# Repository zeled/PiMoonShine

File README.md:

# PiMoonShine
Все для автоматики Винокура на Orange PI PC+

Основано на Node-Red
18b20-mqtt - сервис опрашивающий 18b20 датчики и засылающий их в mqtt

---

## Установка Armbian на Orange PI PC+
https://www.armbian.com/orange-pi-pc-plus/

Устанавливаем Armbian Focal

Через armbian-config настраиваем сеть, доступ по ssh, timezone и т.д.

Там же в System-Hardware включаем i2c0, uart1, w1-gpio

## Установка Node-RED и необходимые пакеты
#### Заходим по SSH на OrangePi под рутом и запускаем:
```
bash <(curl -sL https://raw.githubusercontent.com/node-red/linux-installers/master/deb/update-nodejs-and-nodered)

apt-get update&&apt-get upgrade&&apt-get install mosquitto mosquitto-clients nginx

pip3 install paho-mqtt
pip3 install w1thermsensor
```
---
#### Копируем из папки 18b20-mqtt:

>18b20-mqtt в /usr/local/bin/

>18b20-mqtt.service в /etc/systemd/system/

#### Копируем из папки nginx:

>nodered в /etc/nginx/sites-enabled/

---
#### Запускаем:
`systemctl daemon-reload&&systemctl restart mosquitto 18b20-mqtt nodered nginx`

## Первоначальная Настройка

Заходим через браузер на http://<ip адресс orange-pi>/

Далее в "Управление палитрой"

#### Устанавилваем узлы:
>node-red-contrib-bme280
>
>node-red-contrib-configurable-interval
>
>node-red-contrib-mytimeout
>
>node-red-contrib-opi-gpio
>
>node-red-contrib-simpletime
>
>node-red-contrib-telegrambot
>
>node-red-contrib-ui-led
>
>node-red-contrib-ui-svg
>
>node-red-dashboard
>
>node-red-node-serialport

---

Импортируем проект из PiMoonShine.json

Настриваем telegram бота под свои данные.

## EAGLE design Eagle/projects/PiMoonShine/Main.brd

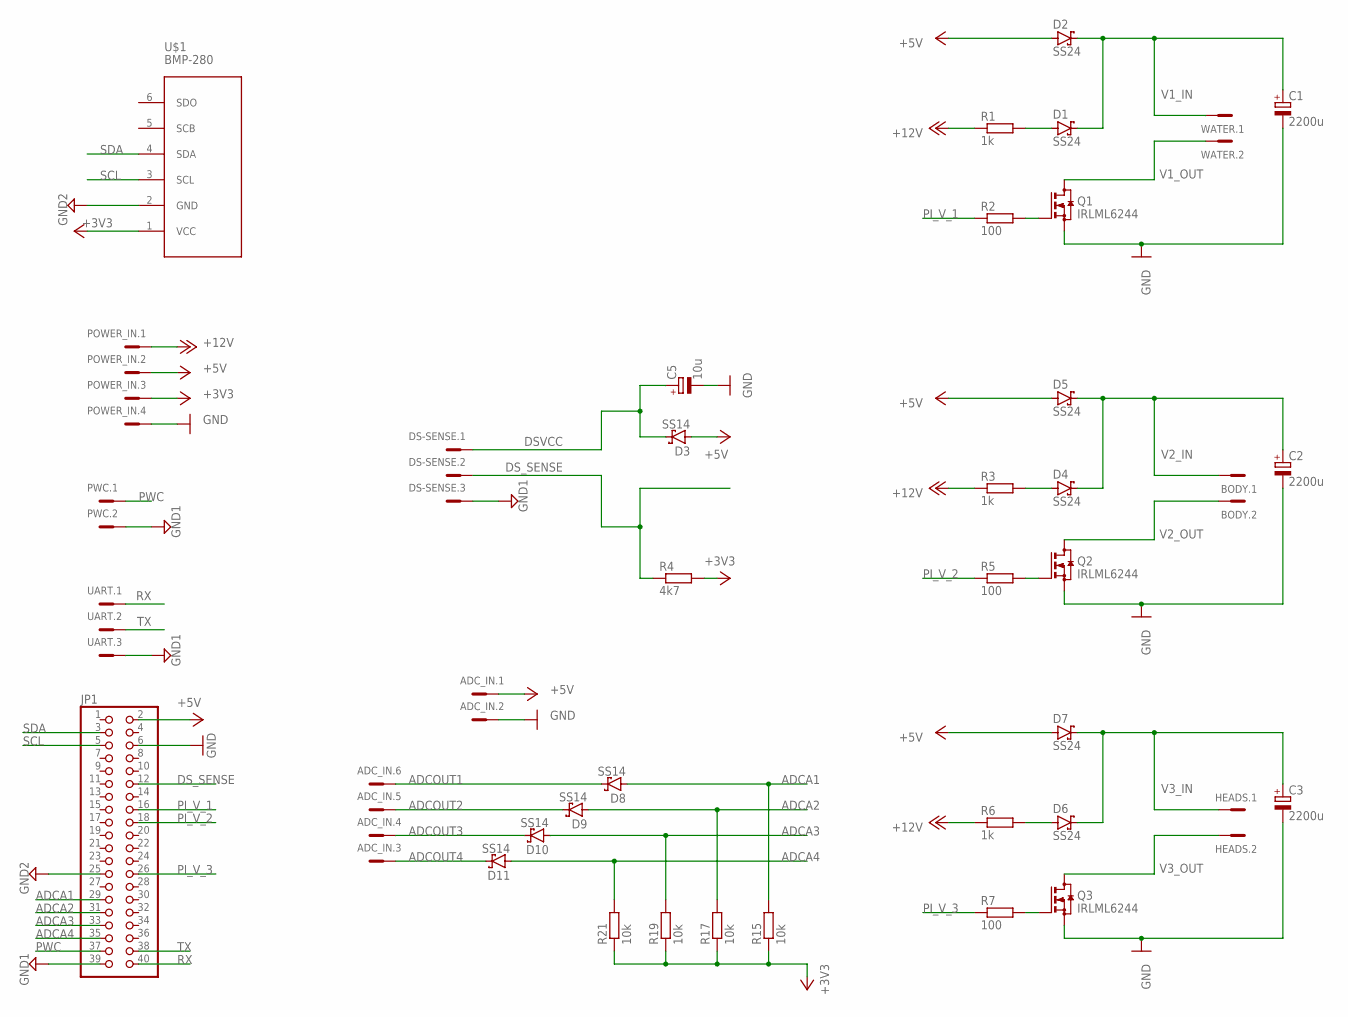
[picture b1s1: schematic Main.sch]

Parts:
ADC_IN: MCV6
BODY: MCV2
C1, C2, C3: 2200u; TT5D10
C5: 10u; SMC_B
D1, D2, D4, D5, D6, D7: SS24; SMB
D3, D8, D9, D10, D11: SS14; SMA
DS-SENSE: MCV3
HEADS: MCV2
JP1: PINHD-2X20; 2X20
POWER_IN: MCV4
PWC: MCV2
Q1, Q2, Q3: IRLML6244; SOT23
R1, R3, R6: 1k; R1206
R2, R5, R7: 100; R1206
R4: 4k7; R1206
R15, R17, R19, R21: 10k; R1206
U$1: BMP-280; BPM-280
UART: MCV3
WATER: MCV2

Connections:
+3V3: POWER_IN.3, R4.2, R15.1, R17.1, R19.1, R21.1, U$1.1 (VCC)
+5V: ADC_IN.1, D2.A, D3.A, D5.A, D7.A, JP1.2, POWER_IN.2
+12V: POWER_IN.1, R1.1, R3.1, R6.1
ADCA1: D8.A, JP1.29, R15.2
ADCA2: D9.A, JP1.31, R17.2
ADCA3: D10.A, JP1.33, R19.2
ADCA4: D11.A, JP1.35, R21.2
ADCOUT1: ADC_IN.6, D8.C
ADCOUT2: ADC_IN.5, D9.C
ADCOUT3: ADC_IN.4, D10.C
ADCOUT4: ADC_IN.3, D11.C
DSVCC: C5.+, D3.C, DS-SENSE.1
DS_SENSE: DS-SENSE.2, JP1.12, R4.1
GND: ADC_IN.2, C1.-, C2.-, C3.-, C5.-, JP1.6, POWER_IN.4, Q1.2 (S), Q2.2 (S), Q3.2 (S)
GND1: DS-SENSE.3, JP1.39, PWC.2, UART.3
GND2: JP1.25, U$1.2 (GND)
unnamed: D1.A, R1.2
unnamed: D4.A, R3.2
unnamed: Q1.1 (G), R2.2
unnamed: Q2.1 (G), R5.2
unnamed: D6.A, R6.2
unnamed: Q3.1 (G), R7.2
PI_V_1: JP1.16, R2.1
PI_V_2: JP1.18, R5.1
PI_V_3: JP1.26, R7.1
PWC: JP1.37, PWC.1
RX: JP1.40, UART.1
SCL: JP1.5, U$1.3 (SCL)
SDA: JP1.3, U$1.4 (SDA)
TX: JP1.38, UART.2
V1_IN: C1.+, D1.C, D2.C, WATER.1
V1_OUT: Q1.3 (D), WATER.2
V2_IN: BODY.1, C2.+, D4.C, D5.C
V2_OUT: BODY.2, Q2.3 (D)
V3_IN: C3.+, D6.C, D7.C, HEADS.1
V3_OUT: HEADS.2, Q3.3 (D)

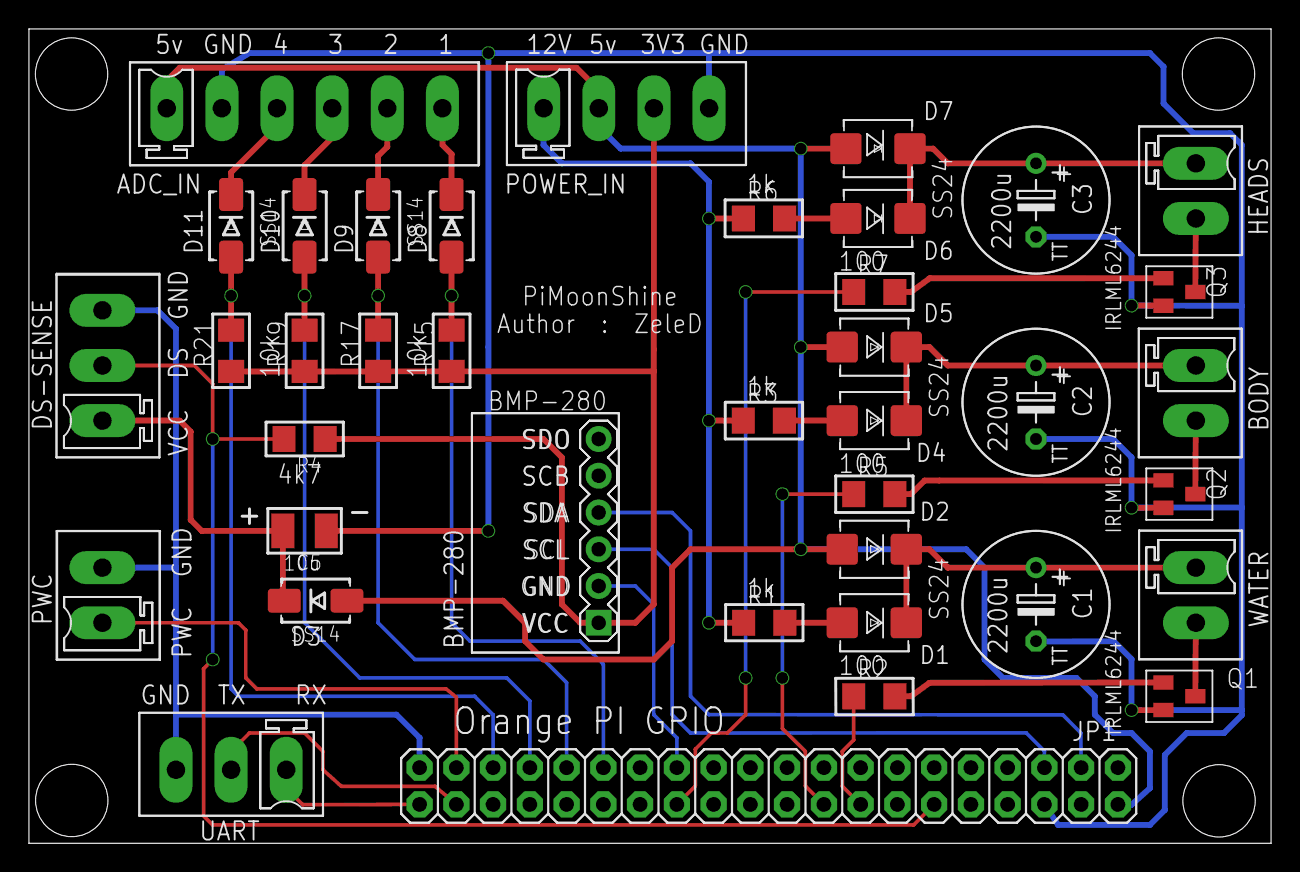
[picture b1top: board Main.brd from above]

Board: 2 copper layers, 85.8 x 56.3 mm, 39 parts (0 on the bottom side), 36 nets.

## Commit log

2021-02-11 Added 18b20 service Added initial PiMoonShine.json
2021-02-11 Change README.md
2021-02-11 Локализация графиков
2021-02-11 Добавлен функционал для Telegram Бота
2021-04-30 Added main configs and Eagle files
